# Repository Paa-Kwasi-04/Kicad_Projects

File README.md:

# KiCad Projects Repository

This repository contains a collection of KiCad PCB design projects covering various electronics applications from power supplies to microcontroller boards and automation systems.

## Projects Overview

### Power and Control Systems

#### [8 Channel Relay](8_ChannelRelay/)
An 8-channel relay board for controlling multiple high-power devices, suitable for home automation and industrial control applications.

#### [ACDC Convertor](ACDC_Convertor/)
AC-to-DC converter circuit with rectification, filtering, and voltage regulation for stable DC power output from AC sources.

#### [Buck Convertor 4-Layer Board](Buck_Convertor_4_layers/)
4-layer PCB design for a buck convertor (step-down DC-DC convertor) with enhanced thermal management and EMI performance for efficient power supply applications.

#### [Battery Power Management Board 4-Layer](Battery_Power_Management_Board_4_layers/)
4-layer PCB design for a complete lithium-ion/polymer battery management system featuring TP4056 charger IC and DW01A protection IC with USB Type-C charging interface for portable electronics and IoT applications.

#### [Simple Power Supply Board](Simple_power_supply_board/)
A regulated DC power supply with filtering and protection circuitry for powering electronic projects.

#### [Motor Driver 4-Layer Board](Motor_Driver_4_layer/)
4-layer PCB design for a brushed DC motor driver featuring DRV8871DDA H-bridge driver with PWM control, supporting up to 45V and 3.6A with current limiting protection for efficient motor control applications.

#### [Stepper Motor Driver 4-Layer Board](Stepper_Motor_Driver_4_layers/)
4-layer PCB design for a stepper motor driver featuring A4988 driver IC with microstepping support (up to 1/16 step), supporting up to 35V and 2A per coil with built-in protection for CNC machines, 3D printers, and robotics applications.

### Microcontroller Boards

#### [ESP32 Dev Board Clone](ESP32%20Dev%20Board%20Clone/)
Custom ESP32 development board with Wi-Fi and Bluetooth capabilities for IoT applications.

#### [ESP32 I²C Sensor Hub](ESP32%20I²C%20Sensor%20Hub/)
ESP32-based sensor hub for aggregating data from multiple I²C sensors with wireless transmission capability.

#### [ESP32S3 4-Layer USB-C Board](ESP32S3_4Layer_USB_C/)
Advanced 4-layer PCB design featuring ESP32-WROOM-32 module with USB-C connectivity for professional embedded and IoT applications with improved signal integrity and EMC performance.

#### [ESP32 Memory Display Board](ESP32_mem_display/)
ESP32-based board with integrated ILI9341 320x240 SPI TFT LCD display and W25Q128JVS external SPI flash memory for IoT applications requiring user interface and data logging capabilities.

### Industrial Automation

#### [Conveyor Belt Main Board](Conveyor_Belt_Main_Board/)
Complete control board for automated conveyor systems featuring ATmega328P, stepper motor driver, I2C multiplexer, and IR sensor support.

#### [Conveyor Belt Arduino Mega Board](Conveyor_Belt_Arduino_mega_board/)
Arduino Mega interface board for conveyor belt control with integrated power and signal conditioning.

### Sensors and Monitoring

#### [Car Battery Level Detector](CarBatteryLevelDetector/)
12V automotive battery voltage monitoring circuit with state of charge indication.

#### [Sensor and Display Module](Sensor%20and%20Display%20Module/)
Integrated board combining sensor inputs with display output for real-time data visualization.

### Audio and Visual

#### [Stereo Audio Processing Board](Stereo_Audio_Processing_Board/)
Stereo audio signal processing board for amplification and filtering with left/right channel support.

#### [Chaser Board](Chaser%20Board/)
LED chaser circuit creating sequential lighting effects for decorative and indicator applications.

### Other Projects

#### [Mosquito Repellant](MosquitoRepellant/)
Electronic mosquito repellent device providing chemical-free pest control.

## Tools Used

All projects are designed using **KiCad**, an open-source electronics design automation suite.

## Project Structure

Each project directory contains:
- KiCad project files (`.kicad_pro`, `.kicad_sch`, `.kicad_pcb`)
- README.md with project description and features
- PCB preview images
- Additional documentation where applicable

## Getting Started

1. Install [KiCad](https://www.kicad.org/) (version 6.0 or later recommended)
2. Clone this repository
3. Open any project by double-clicking the `.kicad_pro` file
4. Review the schematic and PCB layout
5. Modify as needed for your application

## License

Please check individual project directories for specific licensing information.

## Contributing

This is a personal project repository. Feel free to use these designs as reference for your own projects.

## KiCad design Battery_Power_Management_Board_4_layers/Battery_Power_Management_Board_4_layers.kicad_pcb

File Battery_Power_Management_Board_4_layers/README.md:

# Battery Power Management Board 4-Layer

## Description
This is a 4-layer PCB design for a complete lithium-ion/polymer battery power management system. The board integrates battery charging, protection, and power distribution functionality. The 4-layer stackup provides improved thermal management, better power distribution, and enhanced electromagnetic compatibility. This design is ideal for portable electronics, IoT devices, and any application requiring safe and efficient single-cell Li-ion/LiPo battery management.

## Features
- 4-layer PCB design for optimal performance:
  - Enhanced thermal dissipation
  - Improved power plane distribution
  - Better EMI/EMC characteristics
  - Reduced electrical noise
- TP4056 standalone linear battery charger IC
  - 1A charging current capability
  - 4.2V ±1% charge voltage precision
  - Input voltage range: 4.0V to 8.0V
  - Suitable for single-cell Li-ion/LiPo batteries
- DW01A battery protection IC
  - Overcharge protection
  - Over-discharge protection
  - Overcurrent protection
  - Short circuit protection
- USB Type-C connector for charging
- Battery connection terminals
- LED charging status indicators
- Compact and professional layout

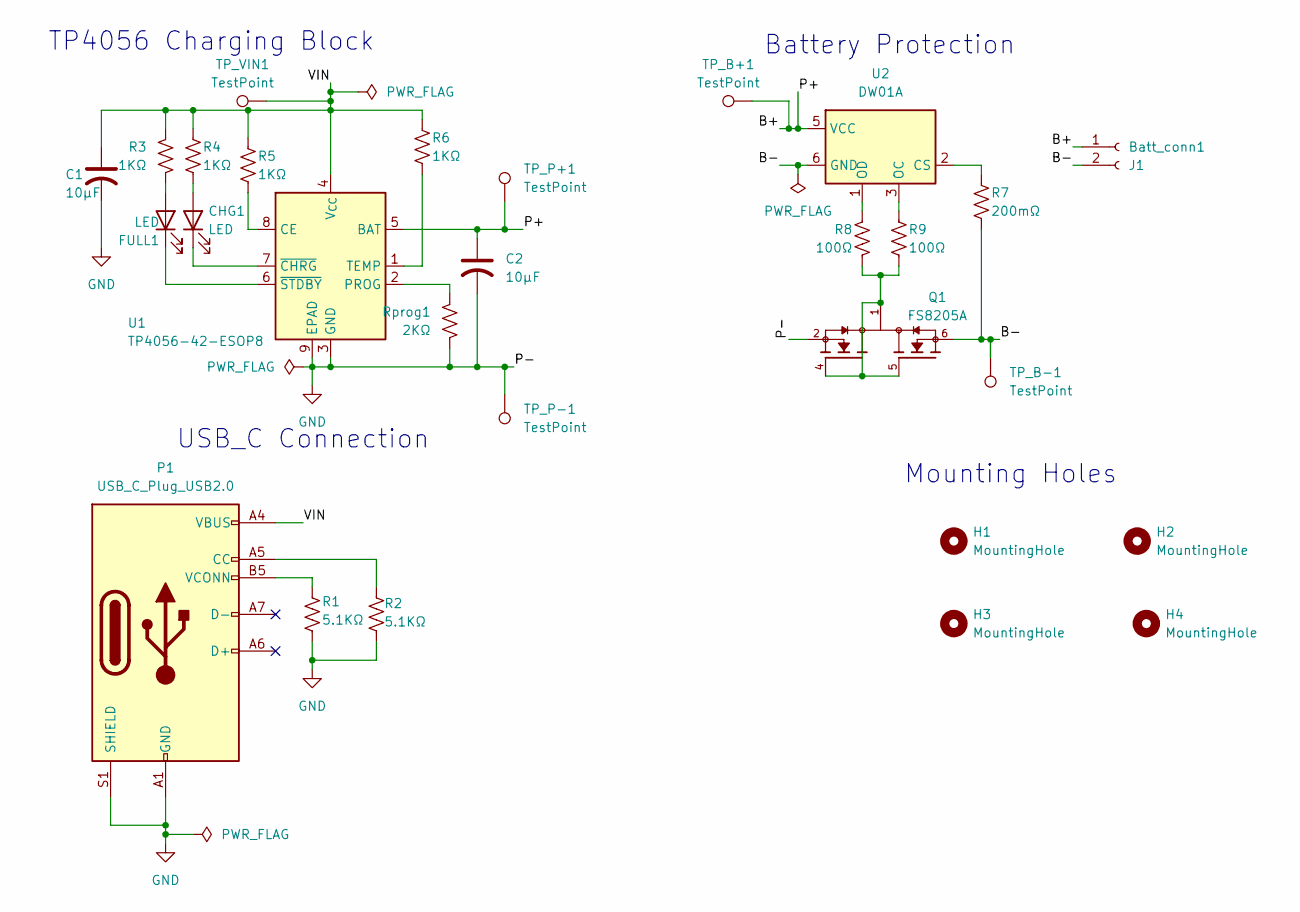
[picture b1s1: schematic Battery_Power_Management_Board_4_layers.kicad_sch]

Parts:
Batt_conn1: J1; JST_GH_BM02B-GHS-TBT_1x02-1MP_P1.25mm_Vertical
C1, C2: 10µF; C_0201_0603Metric
CHG1: LED; LED_0201_0603Metric
FULL1: LED; LED_0201_0603Metric
H1, H2, H3, H4: MountingHole; MountingHole_2.2mm_M2_DIN965_Pad
P1: USB_C_Plug_USB2.0; USB_C_Receptacle_GCT_USB4085
Q1: FS8205A; HSOP-8-1EP_3.9x4.9mm_P1.27mm_EP2.41x3.1mm; PARTREV 1.7
R1, R2: 5.1KΩ; R_0603_1608Metric
R3, R4, R5, R6: 1KΩ; R_0603_1608Metric
R7: 200mΩ; R_0603_1608Metric
R8, R9: 100Ω; R_0603_1608Metric
Rprog1: 2KΩ; R_0603_1608Metric
TP_B+1: TestPoint; TestPoint_THTPad_D1.0mm_Drill0.5mm
TP_B-1: TestPoint; TestPoint_THTPad_D1.0mm_Drill0.5mm
TP_P+1: TestPoint; TestPoint_THTPad_D1.0mm_Drill0.5mm
TP_P-1: TestPoint; TestPoint_THTPad_D1.0mm_Drill0.5mm
TP_VIN1: TestPoint; TestPoint_THTPad_D1.0mm_Drill0.5mm
U1: TP4056-42-ESOP8; HSOP-8-1EP_3.9x4.9mm_P1.27mm_EP2.41x3.1mm
U2: DW01A; SOT-23-6

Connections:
/B+: Batt_conn1.1, C2.1, TP_B+1.1, TP_P+1.1, U1.5 (BAT), U2.5 (VCC)
/B-: Batt_conn1.2, Q1.6, Q1.7, R7.2, TP_B-1.1, U2.6 (GND)
/VIN: C1.1, P1.A4 (VBUS), P1.A9 (VBUS), P1.B4 (VBUS), P1.B9 (VBUS), R3.1, R4.1, R5.1, R6.1, TP_VIN1.1, U1.4 (V_{CC})
GND: C1.2, C2.2, P1.A1 (GND), P1.A12 (GND), P1.B1 (GND), P1.B12 (GND), P1.S1 (SHIELD), Q1.2, Q1.3, R1.2, R2.2, Rprog1.2, TP_P-1.1, U1.3 (GND), U1.9 (EPAD)
unnamed: CHG1.2 (A), R4.2
unnamed: CHG1.1 (K), U1.7 (~CHRG)
unnamed: FULL1.2 (A), R3.2
unnamed: FULL1.1 (K), U1.6 (~STDBY)
unnamed: P1.A5 (CC), R2.1
unnamed: P1.B5 (VCONN), R1.1
unnamed: Q1.1, Q1.4, Q1.5, Q1.8, R8.2, R9.2
unnamed: R5.2, U1.8 (CE)
unnamed: Rprog1.1, U1.2 (PROG)
unnamed: R6.2, U1.1 (TEMP)
unnamed: R7.1, U2.2 (CS)
unnamed: R9.1, U2.3 (OC)
unnamed: R8.1, U2.1 (OD)

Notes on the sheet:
Battery Protection
USB_C Connection
Mounting Holes
TP4056 Charging Block

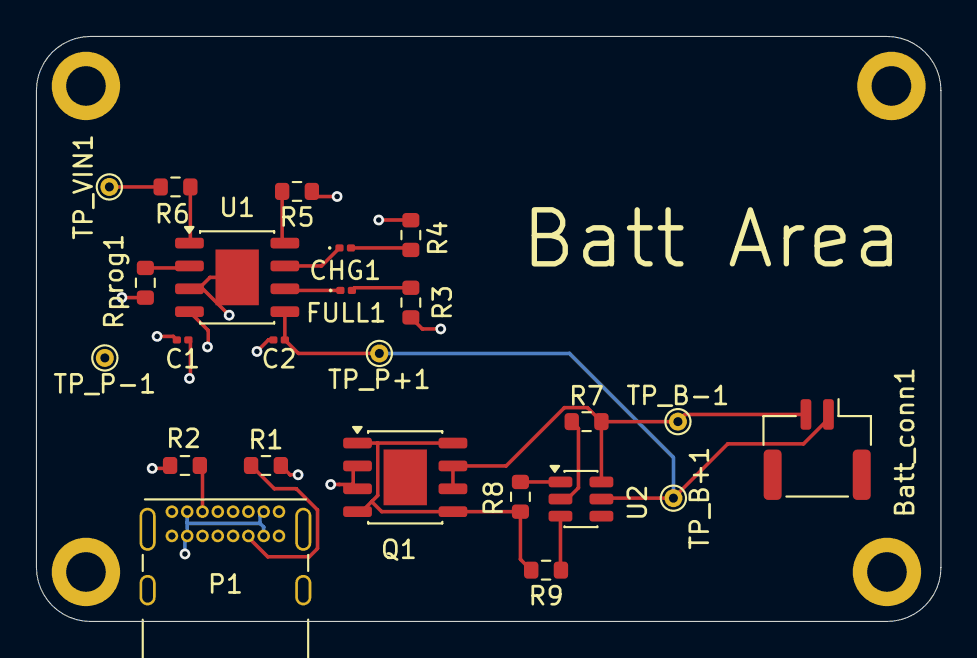
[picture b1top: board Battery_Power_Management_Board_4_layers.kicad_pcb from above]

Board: 4 copper layers, 50.2 x 32.5 mm, 28 parts (0 on the bottom side), 17 nets.

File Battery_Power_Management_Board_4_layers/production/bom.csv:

Designator,Footprint,Quantity,Value,LCSC Part #
BATT_CONN1,JST_GH_BM02B-GHS-TBT_1x02-1MP_P1.25mm_Vertical,1,J1,
"C1, C2",0201,2,10µF,
"CHG1, FULL1",0201,2,LED,
P1,USB_C_Receptacle_GCT_USB4085,1,USB_C_Plug_USB2.0,
Q1,HSOP-8-1EP_3.9x4.9mm_P1.27mm_EP2.41x3.1mm,1,FS8205A,
"R1, R2",0603,2,5.1KΩ,
"R3, R4, R5, R6",0603,4,1KΩ,
R7,0603,1,200mΩ,
"R8, R9",0603,2,100Ω,
RPROG1,0603,1,2KΩ,
"TP_B+1, TP_B-1, TP_P+1, TP_P-1, TP_VIN1",TestPoint_THTPad_D1.0mm_Drill0.5mm,5,TestPoint,
U1,HSOP-8-1EP_3.9x4.9mm_P1.27mm_EP2.41x3.1mm,1,TP4056-42-ESOP8,
U2,SOT-23-6,1,DW01A,

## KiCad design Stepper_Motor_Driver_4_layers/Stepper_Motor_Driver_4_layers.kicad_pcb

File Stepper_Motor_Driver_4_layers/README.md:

# Stepper Motor Driver 4-Layer Board

## Description
This is a 4-layer PCB design for a stepper motor driver circuit featuring the A4988 stepper motor driver IC. The 4-layer stackup provides improved thermal management, better power distribution, and enhanced electromagnetic compatibility. This driver board supports microstepping control for smooth motor operation and is capable of driving bipolar stepper motors with high efficiency and built-in protection features.

## Features
- 4-layer PCB design for optimal performance:
  - Enhanced thermal dissipation
  - Improved power plane distribution
  - Better EMI/EMC characteristics
  - Reduced electrical noise
- A4988 stepper motor driver IC (Pololu compatible)
- Microstepping support (full, half, 1/4, 1/8, 1/16 step modes)
- Operating voltage up to 35V
- Continuous output current up to 2A per coil
- Built-in translator for step and direction control
- Overcurrent and thermal shutdown protection
- Compatible with standard microcontroller interfaces
- Screw terminal connections for motor and power
- Pin header for control signals
- Suitable for CNC machines, 3D printers, and robotics applications
- Compact and professional layout

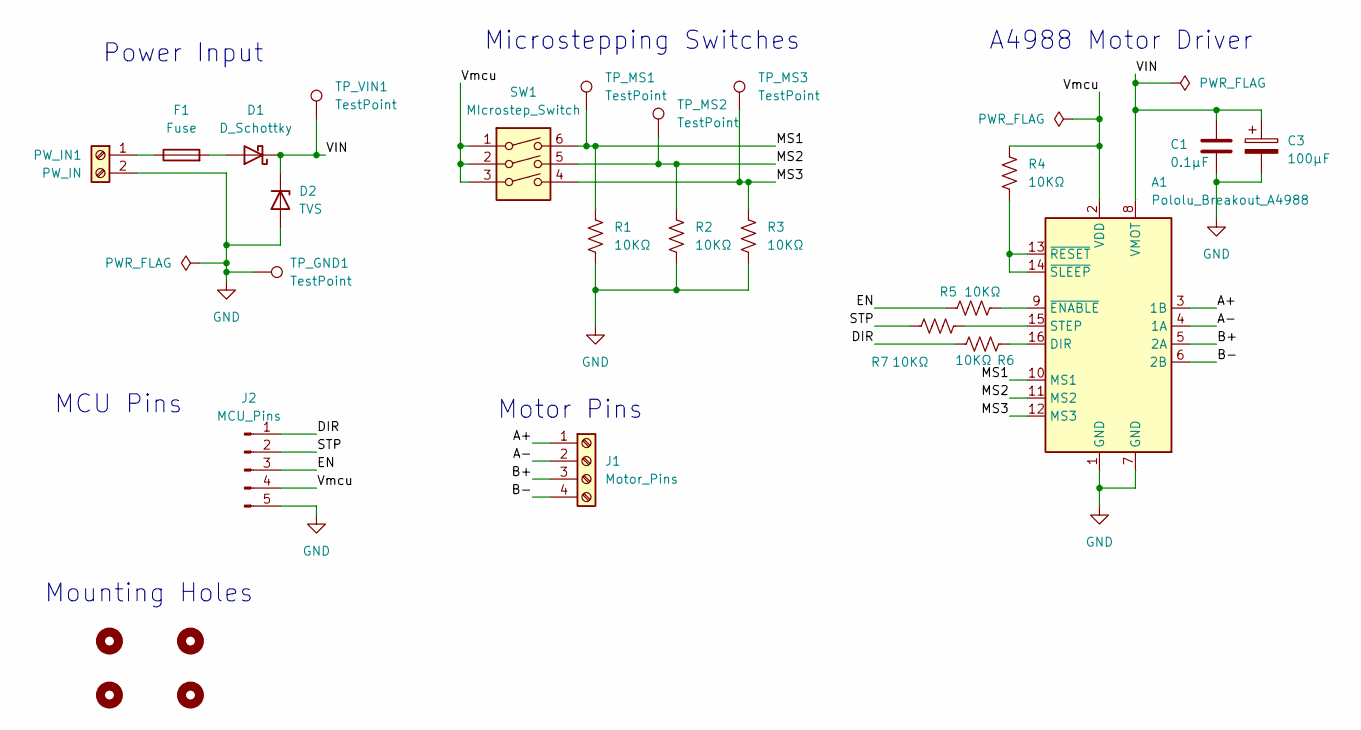
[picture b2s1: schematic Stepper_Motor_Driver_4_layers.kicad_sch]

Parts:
A1: Pololu_Breakout_A4988; Pololu_Breakout-16_15.2x20.3mm
C1: 0.1µF; C_0402_1005Metric
C3: 100µF; C_0402_1005Metric
D1: D_Schottky; D_0603_1608Metric
D2: TVS; D_0603_1608Metric
F1: Fuse; Fuse_BelFuse_0ZRE0005FF_L8.3mm_W3.8mm
H1, H2, H3, H4: MountingHole; MountingHole_2.5mm_Pad
J1: Motor_Pins; JST_GH_BM04B-GHS-TBT_1x04-1MP_P1.25mm_Vertical
J2: MCU_Pins; PinHeader_1x05_P2.54mm_Vertical
PW_IN1: PW_IN; TerminalBlock_Phoenix_MKDS-1,5-2_1x02_P5.00mm_Horizontal
R1, R2, R3, R4, R5, R6, R7: 10KΩ; R_0402_1005Metric
SW1: MIcrostep_Switch; SW_DIP_SPSTx03_Slide_6.7x9.18mm_W6.73mm_P2.54mm_LowProfile_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
TP_GND1: TestPoint; TestPoint_Keystone_5000-5004_Miniature
TP_MS1, TP_MS2, TP_MS3: TestPoint; TestPoint_Keystone_5000-5004_Miniature
TP_VIN1: TestPoint; TestPoint_Keystone_5000-5004_Miniature

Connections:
/A+: A1.3 (1B), J1.1
/A-: A1.4 (1A), J1.2
/B+: A1.5 (2A), J1.3
/B-: A1.6 (2B), J1.4
/DIR: J2.1, R6.2
/EN: J2.3, R5.1
/MS1: A1.10 (MS1), R1.1, SW1.6, TP_MS1.1; also elsewhere on the board
/MS2: A1.11 (MS2), R2.1, SW1.5, TP_MS2.1; also elsewhere on the board
/MS3: A1.12 (MS3), R3.1, SW1.4, TP_MS3.1; also elsewhere on the board
/STP: J2.2, R7.1
/VIN: A1.8 (VMOT), C1.1, C3.1, D1.1 (K), D2.1 (K), TP_VIN1.1
/Vmcu: A1.2 (VDD), J2.4, R4.1, SW1.1, SW1.2, SW1.3; also elsewhere on the board
GND: A1.1 (GND), A1.7 (GND), C1.2, C3.2, D2.2 (A), J2.5, PW_IN1.2, R1.2, R2.2, R3.2, TP_GND1.1
unnamed: A1.16 (DIR), R6.1
unnamed: A1.15 (STEP), R7.2
unnamed: A1.9 (~ENABLE), R5.2
unnamed: A1.13 (~RESET), A1.14 (~SLEEP), R4.2
unnamed: D1.2 (A), F1.2
unnamed: F1.1, PW_IN1.1

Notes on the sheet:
Microstepping Switches
A4988 Motor Driver
Mounting Holes
MCU Pins
Motor Pins
Power Input

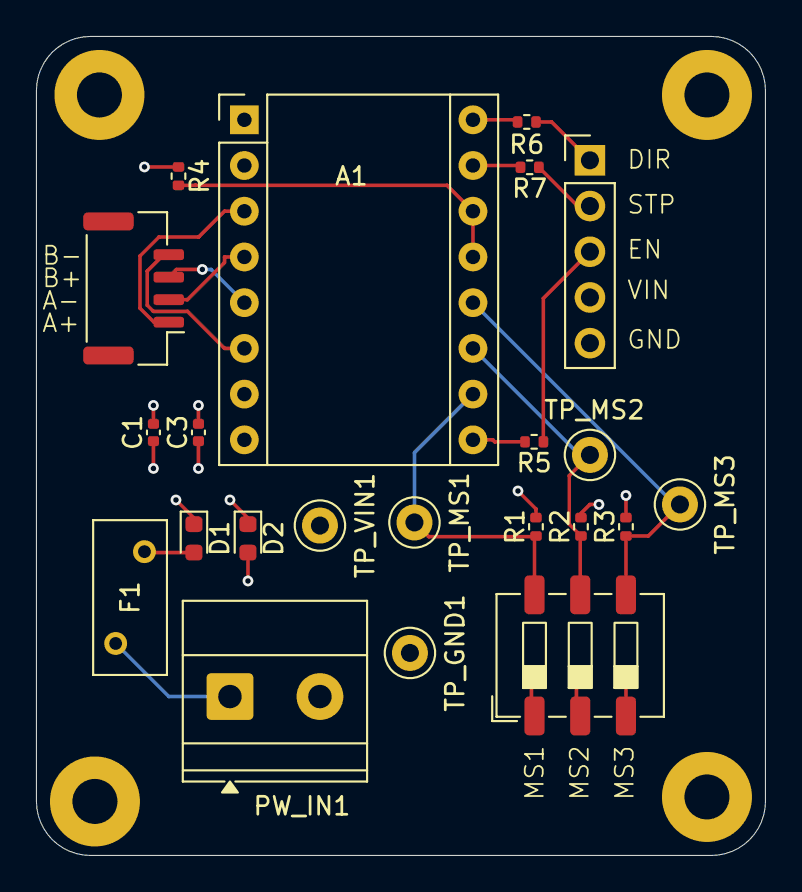
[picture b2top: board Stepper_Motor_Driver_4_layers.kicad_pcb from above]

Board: 4 copper layers, 40.5 x 45.5 mm, 26 parts (0 on the bottom side), 19 nets.

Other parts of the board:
Microstep: Microstep_Switch; SW_DIP_SPSTx03_Slide_6.7x9.18mm_W6.73mm_P2.54mm_LowProfile_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

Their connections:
/MS1: Microstep.6; also elsewhere on the board
/MS2: Microstep.5; also elsewhere on the board
/MS3: Microstep.4; also elsewhere on the board
/Vmcu: Microstep.1, Microstep.2, Microstep.3; also elsewhere on the board

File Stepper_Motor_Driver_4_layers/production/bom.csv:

Designator,Footprint,Quantity,Value,LCSC Part #
A1,Pololu_Breakout-16_15.2x20.3mm,1,Pololu_Breakout_A4988,
C1,0402,1,0.1µF,
C3,0402,1,100µF,
D1,0603,1,D_Schottky,
D2,0603,1,TVS,
F1,Fuse_BelFuse_0ZRE0005FF_L8.3mm_W3.8mm,1,Fuse,
J1,JST_GH_BM04B-GHS-TBT_1x04-1MP_P1.25mm_Vertical,1,Motor_Pins,
J2,PinHeader_1x05_P2.54mm_Vertical,1,MCU_Pins,
MICROSTEP,SW_DIP_SPSTx03_Slide_6.7x9.18mm_W6.73mm_P2.54mm_LowProfile_JPin,1,Microstep_Switch,
PW_IN1,"TerminalBlock_Phoenix_MKDS-1,5-2_1x02_P5.00mm_Horizontal",1,PW_IN,
"R1, R2, R3, R4, R5, R6, R7",0402,7,10KΩ,
"TP_GND1, TP_MS1, TP_MS2, TP_MS3, TP_VIN1",TestPoint_Keystone_5000-5004_Miniature,5,TestPoint,

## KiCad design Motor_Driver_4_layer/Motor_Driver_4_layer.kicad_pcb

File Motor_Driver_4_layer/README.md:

# Motor Driver 4-Layer Board

## Description
This is a 4-layer PCB design for a brushed DC motor driver circuit featuring the DRV8871DDA motor driver IC. The 4-layer stackup provides improved thermal management, better power distribution, and enhanced electromagnetic compatibility. This motor driver board supports PWM control for speed regulation and is capable of driving brushed DC motors with high efficiency and current limiting protection.

## Features
- 4-layer PCB design for optimal performance:
  - Enhanced thermal dissipation
  - Improved power plane distribution
  - Better EMI/EMC characteristics
  - Reduced electrical noise
- DRV8871DDA H-bridge motor driver IC
- PWM control for motor speed regulation
- Operating voltage up to 45V
- Continuous output current up to 3.6A
- Built-in current limiting protection
- Suitable for brushed DC motor control applications
- Compact and professional layout

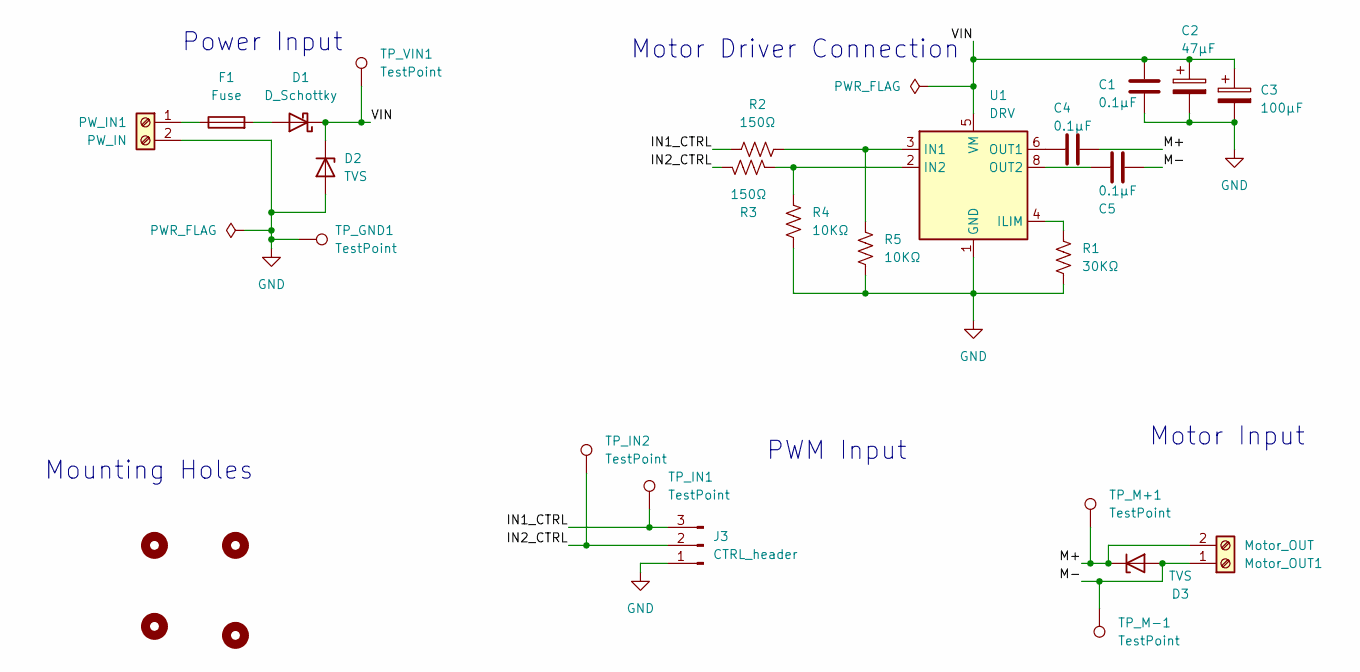
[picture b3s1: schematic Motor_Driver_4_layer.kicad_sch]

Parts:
C1, C4, C5: 0.1µF; C_0402_1005Metric
C2: 47µF; C_0402_1005Metric
C3: 100µF; C_0402_1005Metric
D1: D_Schottky; D_0603_1608Metric
D2, D3: TVS; D_0603_1608Metric
F1: Fuse; Fuse_BelFuse_0ZRE0005FF_L8.3mm_W3.8mm
H1, H2, H3, H4: MountingHole; MountingHole_2.5mm_Pad
J3: CTRL_header; PinHeader_1x03_P2.54mm_Vertical
Motor_OUT1: Motor_OUT; TerminalBlock_Phoenix_MKDS-1,5-2_1x02_P5.00mm_Horizontal
PW_IN1: PW_IN; TerminalBlock_Phoenix_MKDS-1,5-2_1x02_P5.00mm_Horizontal
R1: 30KΩ; R_0402_1005Metric
R2, R3: 150Ω; R_0402_1005Metric
R4, R5: 10KΩ; R_0402_1005Metric
TP_GND1: TestPoint; TestPoint_Keystone_5000-5004_Miniature
TP_IN1, TP_IN2: TestPoint; TestPoint_Keystone_5000-5004_Miniature
TP_M+1: TestPoint; TestPoint_Keystone_5000-5004_Miniature
TP_M-1: TestPoint; TestPoint_Keystone_5000-5004_Miniature
TP_VIN1: TestPoint; TestPoint_Keystone_5000-5004_Miniature
U1: DRV; Texas_HTSOP-8-1EP_3.9x4.9mm_P1.27mm_EP2.95x4.9mm_Mask2.4x3.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

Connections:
/IN1_CTRL: J3.3, R2.2, TP_IN1.1
/IN2_CTRL: J3.2, R3.2, TP_IN2.1
/M+: C4.2, D3.1 (K), Motor_OUT1.2, TP_M+1.1
/M-: C5.2, D3.2 (A), Motor_OUT1.1, TP_M-1.1
/VIN: C1.1, C2.1, C3.1, D1.1 (K), D2.1 (K), TP_VIN1.1, U1.5 (VM); also elsewhere on the board
GND: C1.2, C2.2, C3.2, D2.2 (A), J3.1, PW_IN1.2, R1.2, R4.2, R5.2, TP_GND1.1, U1.1 (GND), U1.7 (GND), U1.9 (GND); also elsewhere on the board
unnamed: D1.2 (A), F1.2
unnamed 7: F1.1, PW_IN1.1; also elsewhere on the board
unnamed 8: R1.1, U1.4 (ILIM); also elsewhere on the board
unnamed 9: R2.1, R5.1, U1.3 (IN1); also elsewhere on the board
unnamed 10: R3.1, R4.1, U1.2 (IN2); also elsewhere on the board
unnamed 11: C4.1, U1.6 (OUT1); also elsewhere on the board
unnamed 12: C5.1, U1.8 (OUT2); also elsewhere on the board

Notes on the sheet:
Mounting Holes
Power Input
Motor Input
PWM Input
Motor Driver Connection

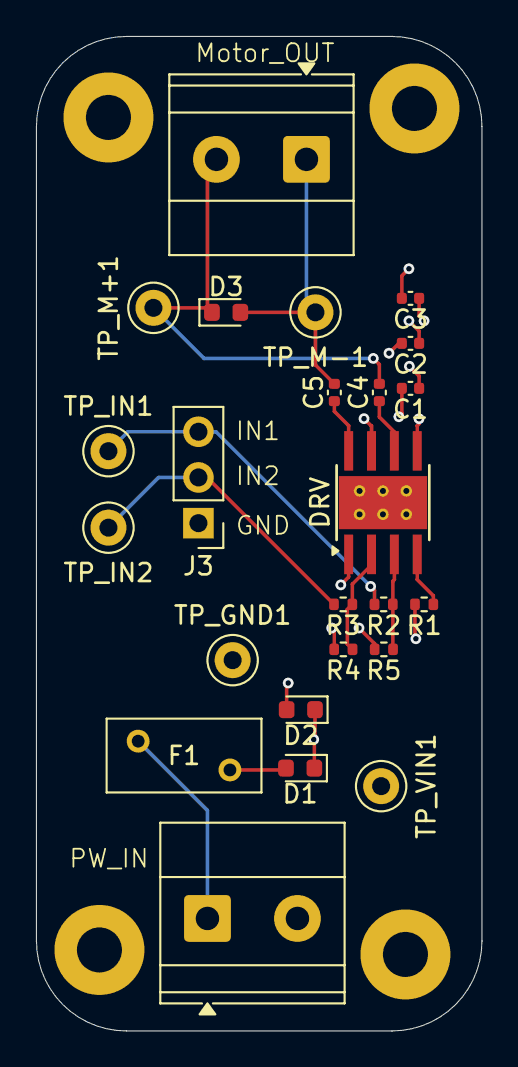
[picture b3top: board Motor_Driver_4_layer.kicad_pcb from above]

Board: 4 copper layers, 24.8 x 55.2 mm, 28 parts (0 on the bottom side), 13 nets.

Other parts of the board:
DRV: DRV; Texas_HTSOP-8-1EP_3.9x4.9mm_P1.27mm_EP2.95x4.9mm_Mask2.4x3.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
PW_IN: PW_IN; TerminalBlock_Phoenix_MKDS-1,5-2_1x02_P5.00mm_Horizontal

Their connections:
/VIN: DRV.5 (VM); also elsewhere on the board
GND: DRV.1 (GND), DRV.7 (GND), DRV.9 (GND), PW_IN.2; also elsewhere on the board
unnamed 7: PW_IN.1; also elsewhere on the board
unnamed 8: DRV.4 (ILIM); also elsewhere on the board
unnamed 9: DRV.3 (IN1); also elsewhere on the board
unnamed 10: DRV.2 (IN2); also elsewhere on the board
unnamed 11: DRV.6 (OUT1); also elsewhere on the board
unnamed 12: DRV.8 (OUT2); also elsewhere on the board

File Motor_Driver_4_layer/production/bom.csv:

Designator,Footprint,Quantity,Value,LCSC Part #
"C1, C4, C5",0402,3,0.1µF,
C2,0402,1,47µF,
C3,0402,1,100µF,
D1,0603,1,D_Schottky,
"D2, D3",0603,2,TVS,
DRV,Texas_HTSOP-8-1EP_3.9x4.9mm_P1.27mm_EP2.95x4.9mm_Mask2.4x3.1mm_ThermalVias,1,DRV,
F1,Fuse_BelFuse_0ZRE0005FF_L8.3mm_W3.8mm,1,Fuse,
J3,PinHeader_1x03_P2.54mm_Vertical,1,CTRL_header,
MOTOR_OUT1,"TerminalBlock_Phoenix_MKDS-1,5-2_1x02_P5.00mm_Horizontal",1,Motor_OUT,
PW_IN,"TerminalBlock_Phoenix_MKDS-1,5-2_1x02_P5.00mm_Horizontal",1,PW_IN,
R1,0402,1,30KΩ,
"R2, R3",0402,2,150Ω,
"R4, R5",0402,2,10KΩ,
"TP_GND1, TP_IN1, TP_IN2, TP_M+1, TP_M-1, TP_VIN1",TestPoint_Keystone_5000-5004_Miniature,6,TestPoint,

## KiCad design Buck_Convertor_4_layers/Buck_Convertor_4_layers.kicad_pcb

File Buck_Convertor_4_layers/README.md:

# Buck Convertor 4-Layer Board

## Description
This is a 4-layer PCB design for a buck convertor (step-down DC-DC convertor) circuit. The 4-layer stackup provides improved thermal management, better power distribution, and enhanced electromagnetic compatibility. Buck convertors are highly efficient switching regulators that step down voltage from a higher input voltage to a lower output voltage, making them ideal for power supply applications.

## Features
- 4-layer PCB design for optimal performance:
  - Enhanced thermal dissipation
  - Improved power plane distribution
  - Better EMI/EMC characteristics
  - Reduced switching noise
- Step-down DC-DC voltage conversion
- High efficiency switching regulator topology
- Suitable for various power supply applications
- Compact and professional layout

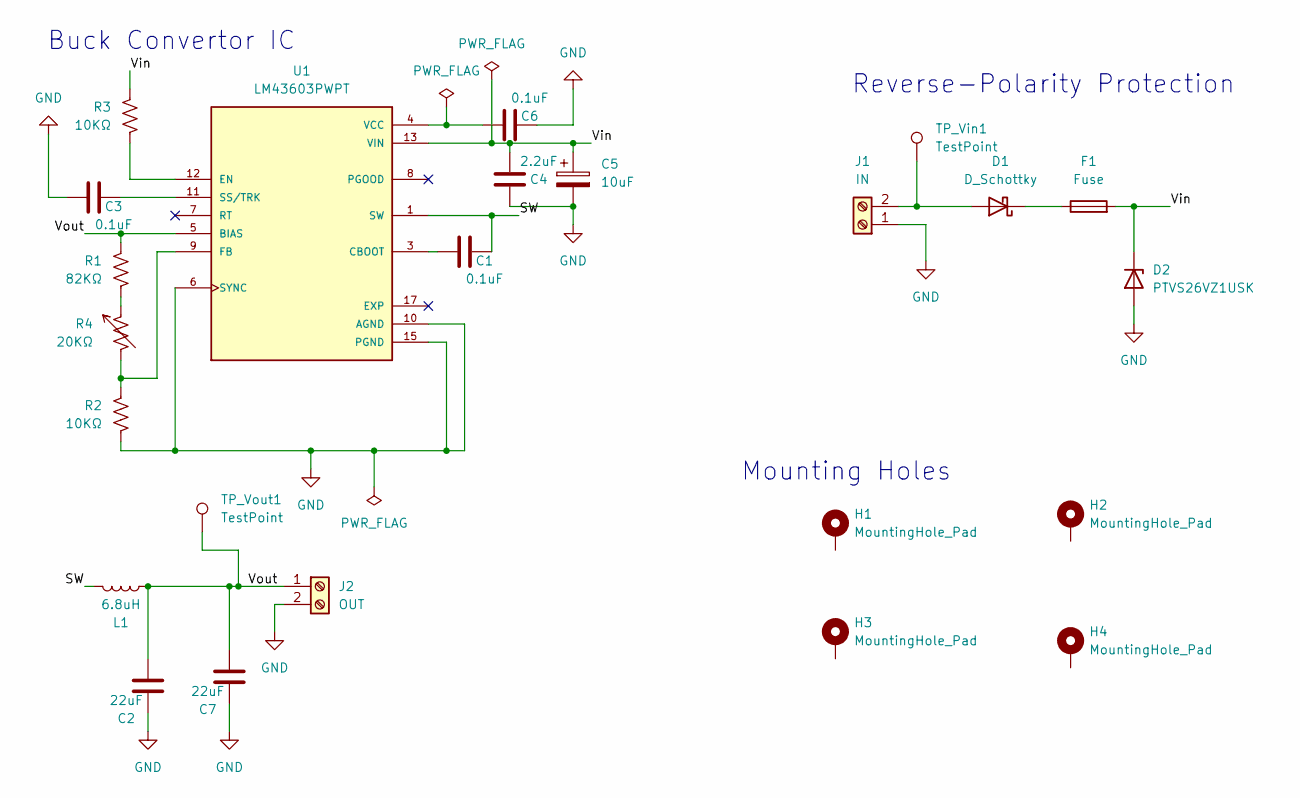
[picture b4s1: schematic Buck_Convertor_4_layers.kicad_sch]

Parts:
C1, C3, C6: 0.1uF; C_0402_1005Metric
C2, C7: 22uF; C_0402_1005Metric
C4: 2.2uF; C_0402_1005Metric
C5: 10uF; C_0402_1005Metric
D1: D_Schottky; D_0603_1608Metric
D2: PTVS26VZ1USK; D_0603_1608Metric
F1: Fuse; Fuse_BelFuse_0ZRE0005FF_L8.3mm_W3.8mm
H1, H2, H3, H4: MountingHole_Pad; MountingHole_2.5mm_Pad
J1: IN; TerminalBlock_Phoenix_MKDS-1,5-2-5.08_1x02_P5.08mm_Horizont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
J2: OUT; TerminalBlock_Phoenix_MKDS-1,5-2-5.08_1x02_P5.08mm_Horizont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
L1: 6.8uH; L_APV_ANR3010
R1: 82KΩ; R_0402_1005Metric
R2, R3: 10KΩ; R_0402_1005Metric
R4: 20KΩ; R_0402_1005Metric
TP_Vin1: TestPoint; TestPoint_Keystone_5000-5004_Miniature
TP_Vout1: TestPoint; TestPoint_Keystone_5000-5004_Miniature
U1: LM43603PWPT; CONV_LM43603PWPT; PARTREV D

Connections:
/SW: C1.2, L1.1, U1.1 (SW), U1.2 (SW)
/Vout: C2.2, C7.2, J2.1, L1.2, R1.1, TP_Vout1.1, U1.5 (BIAS); also elsewhere on the board
GND: C2.1, C3.1, C4.1, C5.2, C6.2, C7.1, D2.2 (A), J1.1, J2.2, R2.2, U1.6 (SYNC), U1.10 (AGND), U1.15 (PGND), U1.16 (PGND), U1.17 (EXP), U1.18, U1.19, U1.20, U1.21, U1.22, U1.23, U1.24, U1.25, U1.26, U1.27, U1.28, U1.29, U1.30, U1.31, U1.32, U1.33, U1.34, U1.35, U1.36, U1.37; also elsewhere on the board
unnamed 3: D1.2 (A), J1.2, TP_Vin1.1; also elsewhere on the board
unnamed: D1.1 (K), F1.1
unnamed: R1.2, R4.1
unnamed: C1.1, U1.3 (CBOOT)
unnamed: R3.2, U1.12 (EN)
unnamed: R2.1, R4.2, U1.9 (FB)
unnamed: C3.2, U1.11 (SS/TRK)
unnamed: C6.1, U1.4 (VCC)
VIN: C4.2, C5.1, D2.1 (K), F1.2, R3.1, U1.13 (VIN), U1.14 (VIN)

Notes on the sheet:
Buck Convertor IC
Mounting Holes
Reverse-Polarity Protection

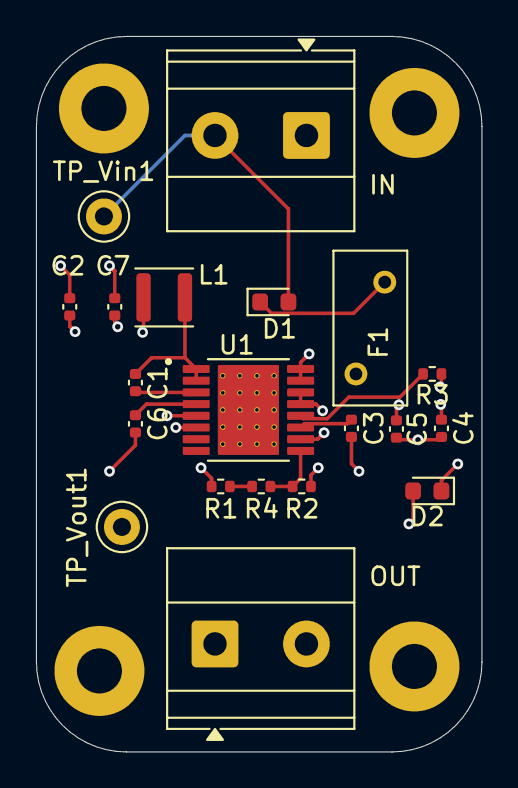
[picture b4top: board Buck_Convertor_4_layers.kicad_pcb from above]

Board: 4 copper layers, 24.8 x 39.8 mm, 24 parts (0 on the bottom side), 12 nets.

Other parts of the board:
IN: IN; TerminalBlock_Phoenix_MKDS-1,5-2-5.08_1x02_P5.08mm_Horizont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
OUT: OUT; TerminalBlock_Phoenix_MKDS-1,5-2-5.08_1x02_P5.08mm_Horizont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

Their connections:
/Vout: OUT.1; also elsewhere on the board
GND: IN.1, OUT.2; also elsewhere on the board
unnamed 3: IN.2; also elsewhere on the board

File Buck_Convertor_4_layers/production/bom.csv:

Designator,Footprint,Quantity,Value,LCSC Part #
"C1, C3, C6",0402,3,0.1uF,
"C2, C7",0402,2,22uF,
C4,0402,1,2.2uF,
C5,0402,1,10uF,
D1,0603,1,D_Schottky,
D2,0603,1,PTVS26VZ1USK,
F1,Fuse_BelFuse_0ZRE0005FF_L8.3mm_W3.8mm,1,Fuse,
IN,"TerminalBlock_Phoenix_MKDS-1,5-2-5.08_1x02_P5.08mm_Horizontal",1,IN,
L1,L_APV_ANR3010,1,6.8uH,
OUT,"TerminalBlock_Phoenix_MKDS-1,5-2-5.08_1x02_P5.08mm_Horizontal",1,OUT,
R1,0402,1,82KΩ,
"R2, R3",0402,2,10KΩ,
R4,0402,1,20KΩ,
"TP_VIN1, TP_VOUT1",TestPoint_Keystone_5000-5004_Miniature,2,TestPoint,
U1,CONV_LM43603PWPT,1,LM43603PWPT,

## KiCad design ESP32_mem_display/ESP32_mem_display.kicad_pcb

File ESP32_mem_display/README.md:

# ESP32 Memory Display Board

## Description
This is an ESP32-based board featuring an integrated SPI TFT LCD display and external SPI flash memory. The board combines wireless connectivity capabilities of the ESP32 with visual output and expandable storage, making it ideal for IoT applications requiring user interface and data logging capabilities.

## Features
- ESP32 module with Wi-Fi and Bluetooth connectivity
- ILI9341 320x240 SPI TFT LCD display
- W25Q128JVS external SPI flash memory (128Mbit / 16MiB)
- SPI interface for high-speed display and memory operations
- Compact design integrating display and storage
- Suitable for IoT dashboards, data loggers, and embedded UI applications

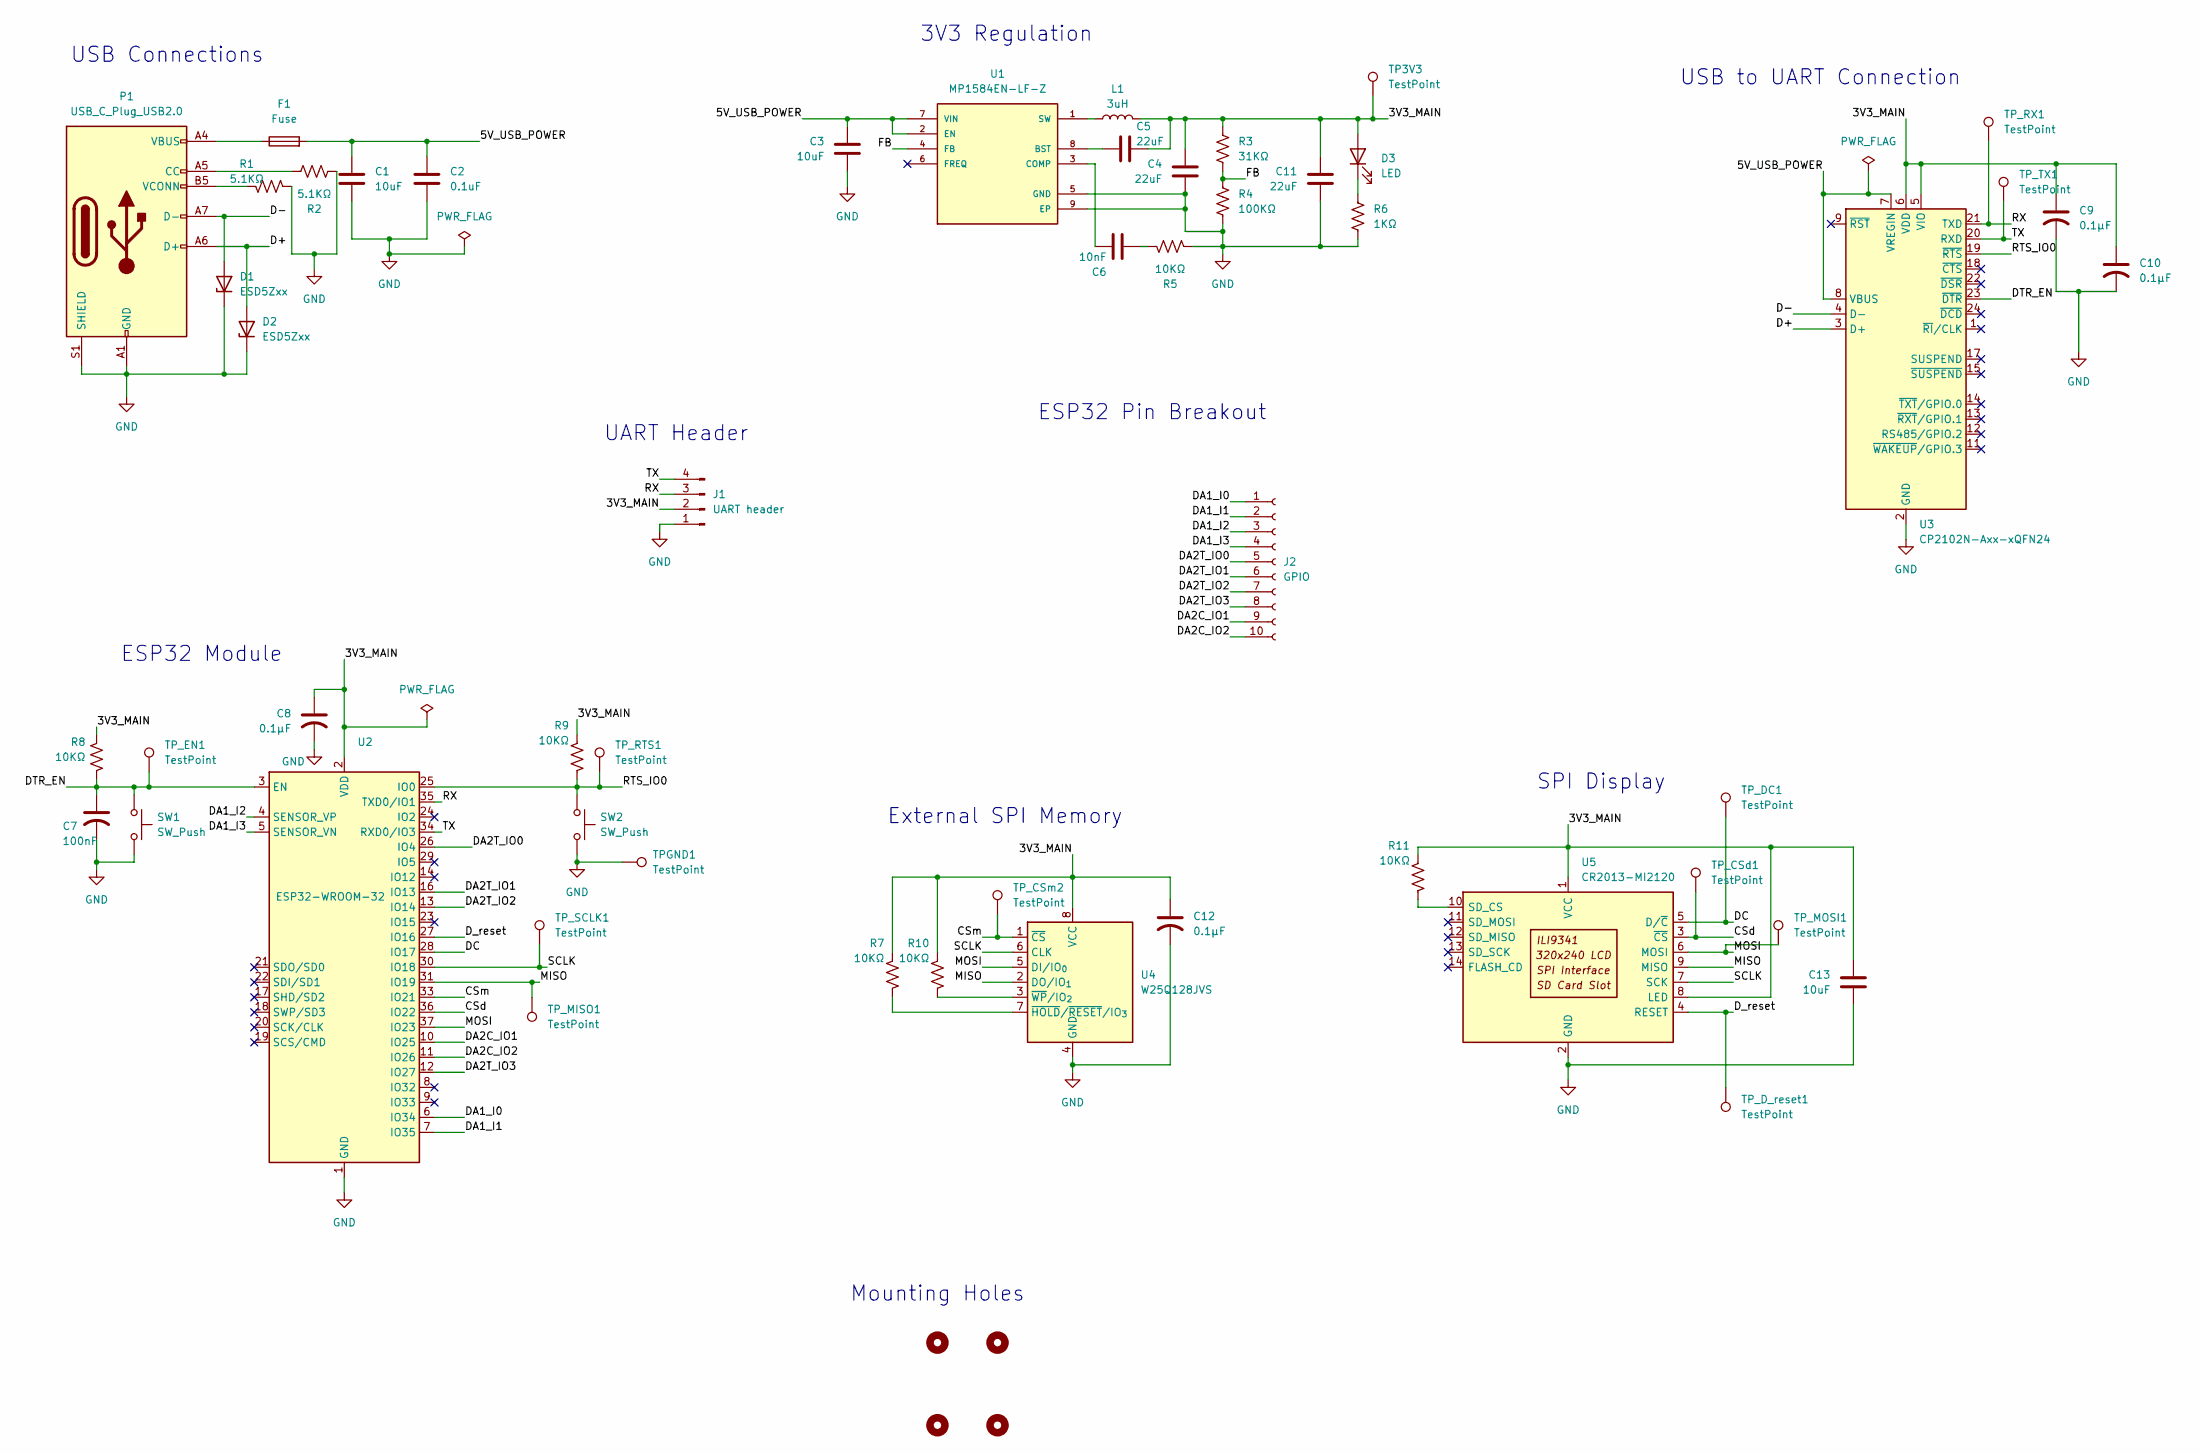
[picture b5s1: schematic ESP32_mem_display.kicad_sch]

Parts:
C1, C3, C13: 10uF; CP_EIA-1608-10_AVX-L
C2: 0.1uF; CP_EIA-1608-10_AVX-L
C4, C5, C11: 22uF; CP_EIA-1608-10_AVX-L
C6: 10nF; CP_EIA-1608-10_AVX-L
C7: 100nF; CP_EIA-1608-10_AVX-L
C8, C9, C10, C12: 0.1µF; CP_EIA-1608-10_AVX-L
D1, D2: ESD5Zxx; D_SOD-523
D3: LED; LED_0402_1005Metric
F1: Fuse; Fuse_BelFuse_0ZRE0025FF_L9.6mm_W3.8mm
H1, H2, H3, H4: MountingHole; MountingHole_3.2mm_M3_Pad
J1: UART header; PinHeader_1x04_P2.54mm_Vertical
J2: GPIO; PinHeader_1x10_P2.54mm_Vertical
L1: 3uH; L_Coilcraft_MSS1246H-XXX
P1: USB_C_Plug_USB2.0; USB_C_Receptacle_GCT_USB4085
R1, R2: 5.1KΩ; R_0201_0603Metric
R3: 31KΩ; R_0201_0603Metric
R4: 100KΩ; R_0201_0603Metric
R5, R7, R8, R9, R10, R11: 10KΩ; R_0201_0603Metric
R6: 1KΩ; R_0201_0603Metric
SW1, SW2: SW_Push; SW_Push_SPST_NO_Alps_SKRK
TP3V3: TestPoint; TestPoint_Keystone_5000-5004_Miniature
TPGND1: TestPoint; TestPoint_Keystone_5000-5004_Miniature
TP_CSd1: TestPoint; TestPoint_Keystone_5000-5004_Miniature
TP_CSm2: TestPoint; TestPoint_Keystone_5000-5004_Miniature
TP_DC1: TestPoint; TestPoint_Keystone_5000-5004_Miniature
TP_D_reset1: TestPoint; TestPoint_Keystone_5000-5004_Miniature
TP_EN1: TestPoint; TestPoint_Keystone_5000-5004_Miniature
TP_MISO1: TestPoint; TestPoint_Keystone_5000-5004_Miniature
TP_MOSI1: TestPoint; TestPoint_Keystone_5000-5004_Miniature
TP_RTS1: TestPoint; TestPoint_Keystone_5000-5004_Miniature
TP_RX1: TestPoint; TestPoint_Keystone_5000-5004_Miniature
TP_SCLK1: TestPoint; TestPoint_Keystone_5000-5004_Miniature
TP_TX1: TestPoint; TestPoint_Keystone_5000-5004_Miniature
U1: MP1584EN-LF-Z; MP1584EN_Buck_convertor
U2: ESP32-WROOM-32
U3: CP2102N-Axx-xQFN24; QFN-24-1EP_4x4mm_P0.5mm_EP2.6x2.6mm
U4: W25Q128JVS; SOIC-8_5.3x5.3mm_P1.27mm
U5: CR2013-MI2120

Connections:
/3V3_MAIN: C4.1, C5.1, C8.1, C9.1, C10.1, C11.1, C12.1, C13.1, D3.2 (A), J1.2, L1.2, R3.1, R7.1, R8.1, R9.1, R10.1, R11.1, TP3V3.1, U2.2 (VDD), U3.5 (VIO), U3.6 (VDD), U4.8 (VCC), U5.1 (VCC), U5.8 (LED)
/5V_USB_POWER: C1.1, C2.1, C3.1, F1.2, U1.2 (EN), U1.7 (VIN), U3.7 (VREGIN), U3.8 (VBUS)
/CSd: TP_CSd1.1, U2.36 (IO22), U5.3 (~CS)
/CSm: TP_CSm2.1, U2.33 (IO21), U4.1 (~CS)
/D+: D2.2 (A), P1.A6 (D+), U3.3 (D+)
/D-: D1.2 (A), P1.A7 (D-), U3.4 (D-)
/DA1_I0: J2.1, U2.6 (IO34)
/DA1_I1: J2.2, U2.7 (IO35)
/DA1_I2: J2.3, U2.4 (SENSOR_VP)
/DA1_I3: J2.4, U2.5 (SENSOR_VN)
/DA2C_IO1: J2.9, U2.10 (IO25)
/DA2C_IO2: J2.10, U2.11 (IO26)
/DA2T_IO0: J2.5, U2.26 (IO4)
/DA2T_IO1: J2.6, U2.16 (IO13)
/DA2T_IO2: J2.7, U2.13 (IO14)
/DA2T_IO3: J2.8, U2.12 (IO27)
/DC: TP_DC1.1, U2.28 (IO17), U5.5 (D/~C)
/DTR_EN: C7.1, R8.2, SW1.1, TP_EN1.1, U2.3 (EN), U3.23 (~DTR)
/D_reset: TP_D_reset1.1, U2.27 (IO16), U5.4 (RESET)
/FB: R3.2, R4.1, U1.4 (FB)
/MISO: TP_MISO1.1, U2.31 (IO19), U4.2 (DO/IO_{1}), U5.9 (MISO)
/MOSI: TP_MOSI1.1, U2.37 (IO23), U4.5 (DI/IO_{0}), U5.6 (MOSI)
/RTS_IO0: R9.2, SW2.1, TP_RTS1.1, U2.25 (IO0), U3.19 (~RTS)
/RX: J1.3, TP_RX1.1, U2.35 (TXD0/IO1), U3.21 (TXD)
/SCLK: TP_SCLK1.1, U2.30 (IO18), U4.6 (CLK), U5.7 (SCK)
/TX: J1.4, TP_TX1.1, U2.34 (RXD0/IO3), U3.20 (RXD)
GND: C1.2, C2.2, C3.2, C4.2, C7.2, C8.2, C9.2, C10.2, C11.2, C12.2, C13.2, D1.1 (K), D2.1 (K), J1.1, P1.A1 (GND), P1.A12 (GND), P1.B1 (GND), P1.B12 (GND), P1.S1 (SHIELD), R1.2, R2.2, R4.2, R5.2, R6.2, SW1.2, SW2.2, TPGND1.1, U1.5 (GND), U1.9 (EP), U2.1 (GND), U2.15 (GND), U2.38 (GND), U2.39 (GND), U3.2 (GND), U3.25 (GND), U4.4 (GND), U5.2 (GND)
unnamed: C6.2, R5.1
unnamed: D3.1 (K), R6.1
unnamed: F1.1, P1.A4 (VBUS), P1.A9 (VBUS), P1.B4 (VBUS), P1.B9 (VBUS)
unnamed: P1.A5 (CC), R2.1
unnamed: P1.B5 (VCONN), R1.1
unnamed: C5.2, U1.8 (BST)
unnamed: C6.1, U1.3 (COMP)
unnamed: L1.1, U1.1 (SW)
unnamed: R7.2, U4.7 (~HOLD/~RESET/IO_{3})
unnamed: R10.2, U4.3 (~WP/IO_{2})
unnamed: R11.2, U5.10 (SD_CS)

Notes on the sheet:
USB Connections
SPI Display
3V3 Regulation
ESP32 Pin Breakout
USB to UART Connection
UART Header
External SPI Memory
Mounting Holes
ESP32 Module

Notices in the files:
parts and their libraries:
COPYRIGHT: Copyright (C) 2024 Ultra Librarian. All rights reserved.
